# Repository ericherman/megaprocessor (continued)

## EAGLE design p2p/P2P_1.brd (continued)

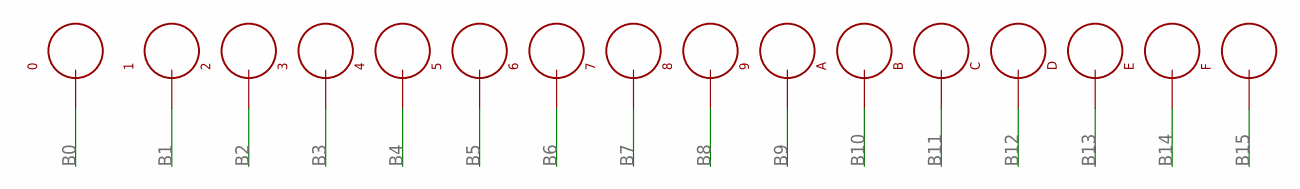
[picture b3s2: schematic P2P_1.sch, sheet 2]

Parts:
0, 1, 2, 3, 4, 5, 6, 7, 8, 9: TEST_LOOP
A: TEST_LOOP
B: TEST_LOOP
C: TEST_LOOP
D: TEST_LOOP
E: TEST_LOOP
F: TEST_LOOP

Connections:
B0: 0.P$1; also elsewhere on the board
B1: 1.P$1; also elsewhere on the board
B2: 2.P$1; also elsewhere on the board
B3: 3.P$1; also elsewhere on the board
B4: 4.P$1; also elsewhere on the board
B5: 5.P$1; also elsewhere on the board
B6: 6.P$1; also elsewhere on the board
B7: 7.P$1; also elsewhere on the board
B8: 8.P$1; also elsewhere on the board
B9: 9.P$1; also elsewhere on the board
B10: A.P$1; also elsewhere on the board
B11: B.P$1; also elsewhere on the board
B12: C.P$1; also elsewhere on the board
B13: D.P$1; also elsewhere on the board
B14: E.P$1; also elsewhere on the board
B15: F.P$1; also elsewhere on the board

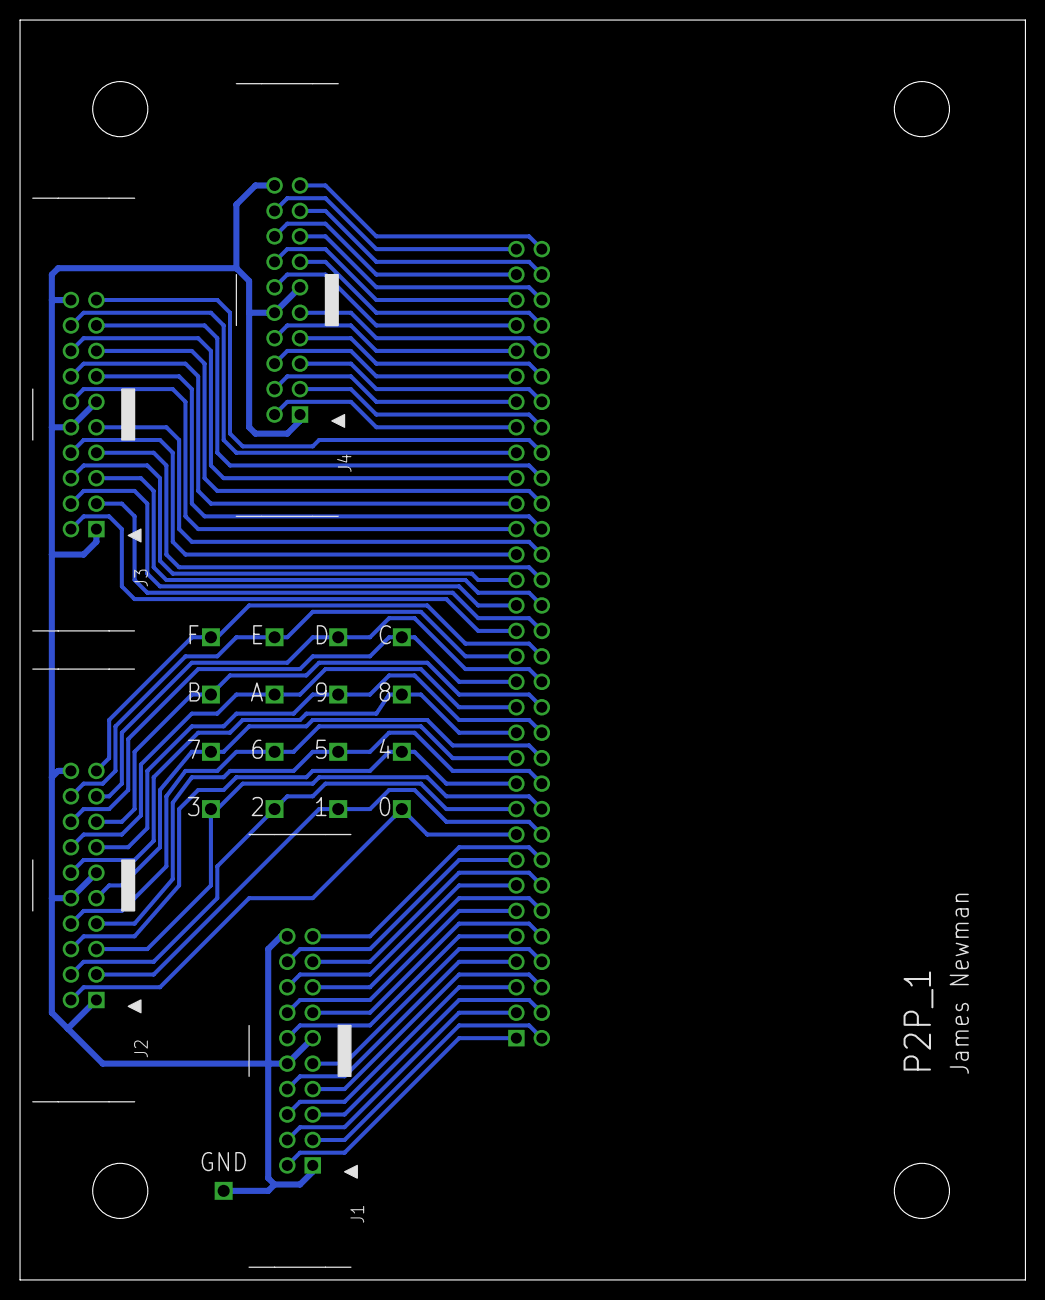
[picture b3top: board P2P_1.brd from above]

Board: 2 copper layers, 100.3 x 125.7 mm, 26 parts (1 on the bottom side), 65 nets.

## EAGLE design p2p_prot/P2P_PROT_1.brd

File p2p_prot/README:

frame to frame (protected)

Does the same as above but I added some protection circuitry for when
its used for incoming buses. I don't know if its necessary, or if I did
it correctly.

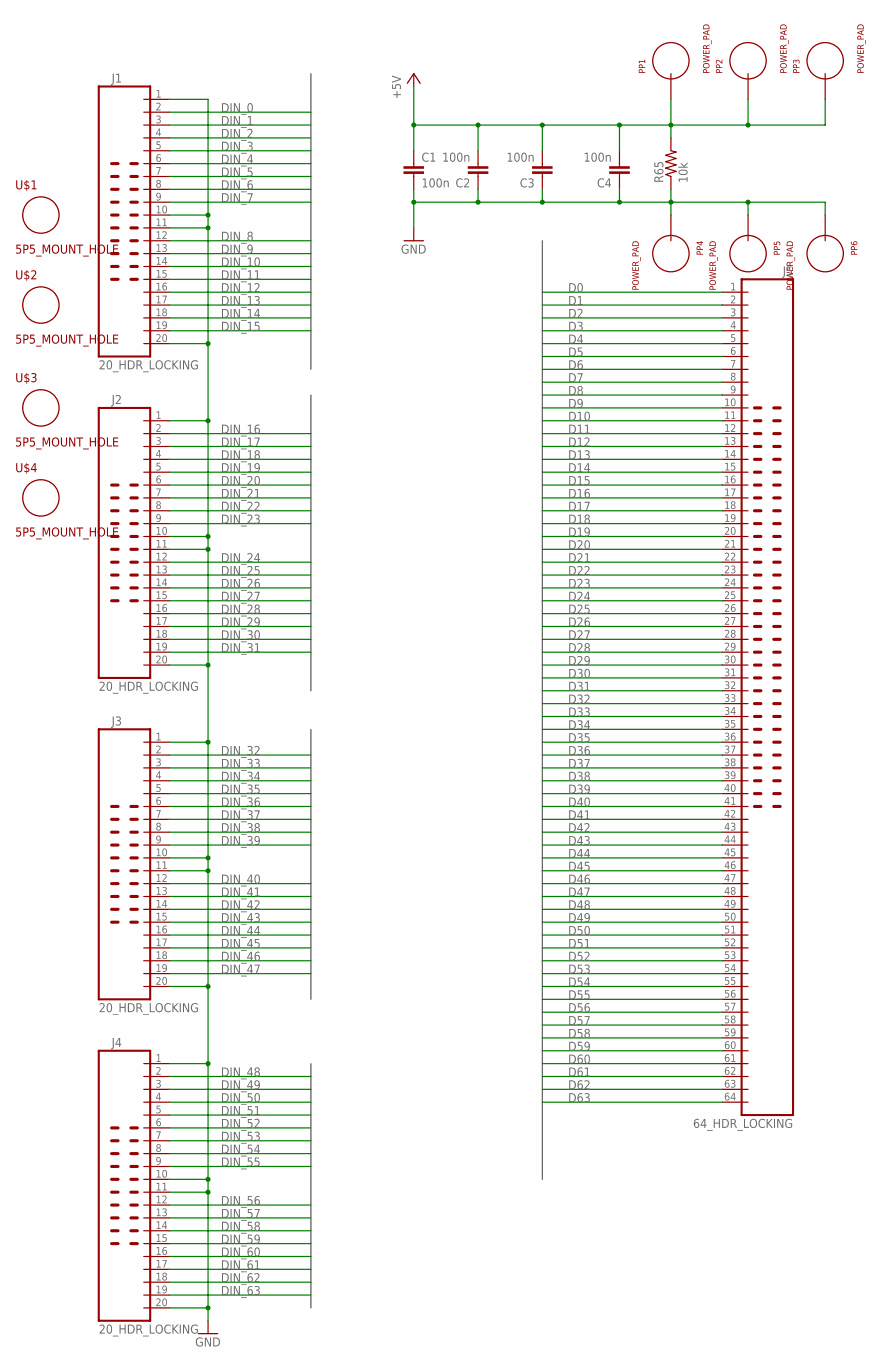
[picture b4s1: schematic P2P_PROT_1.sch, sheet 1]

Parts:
C1, C2, C3, C4: 100n; CAP_P2INCH
J1, J2, J3, J4: 20_HDR_LOCKING
J5: 64_HDR_LOCKING
PP1, PP2, PP3, PP4, PP5, PP6: POWER_PAD
R65: 10k; R_P2INCH
U$1, U$2, U$3, U$4: 5P5_MOUNT_HOLE; 5P5M_HOLE

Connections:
+5V: C1.1, C2.2, C3.2, C4.2, PP1.1, PP2.1, PP3.1, R65.2; also elsewhere on the board
D0: J5.1; also elsewhere on the board
D1: J5.2; also elsewhere on the board
D2: J5.3; also elsewhere on the board
D3: J5.4; also elsewhere on the board
D4: J5.5; also elsewhere on the board
D5: J5.6; also elsewhere on the board
D6: J5.7; also elsewhere on the board
D7: J5.8; also elsewhere on the board
D8: J5.9; also elsewhere on the board
D9: J5.10; also elsewhere on the board
D10: J5.11; also elsewhere on the board
D11: J5.12; also elsewhere on the board
D12: J5.13; also elsewhere on the board
D13: J5.14; also elsewhere on the board
D14: J5.15; also elsewhere on the board
D15: J5.16; also elsewhere on the board
D16: J5.17; also elsewhere on the board
D17: J5.18; also elsewhere on the board
D18: J5.19; also elsewhere on the board
D19: J5.20; also elsewhere on the board
D20: J5.21; also elsewhere on the board
D21: J5.22; also elsewhere on the board
D22: J5.23; also elsewhere on the board
D23: J5.24; also elsewhere on the board
D24: J5.25; also elsewhere on the board
D25: J5.26; also elsewhere on the board
D26: J5.27; also elsewhere on the board
D27: J5.28; also elsewhere on the board
D28: J5.29; also elsewhere on the board
D29: J5.30; also elsewhere on the board
D30: J5.31; also elsewhere on the board
D31: J5.32; also elsewhere on the board
D32: J5.33; also elsewhere on the board
D33: J5.34; also elsewhere on the board
D34: J5.35; also elsewhere on the board
D35: J5.36; also elsewhere on the board
D36: J5.37; also elsewhere on the board
D37: J5.38; also elsewhere on the board
D38: J5.39; also elsewhere on the board
D39: J5.40; also elsewhere on the board
D40: J5.41; also elsewhere on the board
D41: J5.42; also elsewhere on the board
D42: J5.43; also elsewhere on the board
D43: J5.44; also elsewhere on the board
D44: J5.45; also elsewhere on the board
D45: J5.46; also elsewhere on the board
D46: J5.47; also elsewhere on the board
D47: J5.48; also elsewhere on the board
D48: J5.49; also elsewhere on the board
D49: J5.50; also elsewhere on the board
D50: J5.51; also elsewhere on the board
D51: J5.52; also elsewhere on the board
D52: J5.53; also elsewhere on the board
D53: J5.54; also elsewhere on the board
D54: J5.55; also elsewhere on the board
D55: J5.56; also elsewhere on the board
D56: J5.57; also elsewhere on the board
D57: J5.58; also elsewhere on the board
D58: J5.59; also elsewhere on the board
D59: J5.60; also elsewhere on the board
D60: J5.61; also elsewhere on the board
D61: J5.62; also elsewhere on the board
D62: J5.63; also elsewhere on the board
D63: J5.64; also elsewhere on the board
DIN_0: J1.2; also elsewhere on the board
DIN_1: J1.3; also elsewhere on the board
DIN_2: J1.4; also elsewhere on the board
DIN_3: J1.5; also elsewhere on the board
DIN_4: J1.6; also elsewhere on the board
DIN_5: J1.7; also elsewhere on the board
DIN_6: J1.8; also elsewhere on the board
DIN_7: J1.9; also elsewhere on the board
DIN_8: J1.12; also elsewhere on the board
DIN_9: J1.13; also elsewhere on the board
DIN_10: J1.14; also elsewhere on the board
DIN_11: J1.15; also elsewhere on the board
DIN_12: J1.16; also elsewhere on the board
DIN_13: J1.17; also elsewhere on the board
DIN_14: J1.18; also elsewhere on the board
DIN_15: J1.19; also elsewhere on the board
DIN_16: J2.2; also elsewhere on the board
DIN_17: J2.3; also elsewhere on the board
DIN_18: J2.4; also elsewhere on the board
DIN_19: J2.5; also elsewhere on the board
DIN_20: J2.6; also elsewhere on the board
DIN_21: J2.7; also elsewhere on the board
DIN_22: J2.8; also elsewhere on the board
DIN_23: J2.9; also elsewhere on the board
DIN_24: J2.12; also elsewhere on the board
DIN_25: J2.13; also elsewhere on the board
DIN_26: J2.14; also elsewhere on the board
DIN_27: J2.15; also elsewhere on the board
DIN_28: J2.16; also elsewhere on the board
DIN_29: J2.17; also elsewhere on the board
DIN_30: J2.18; also elsewhere on the board
DIN_31: J2.19; also elsewhere on the board
DIN_32: J3.2; also elsewhere on the board
DIN_33: J3.3; also elsewhere on the board
DIN_34: J3.4; also elsewhere on the board
DIN_35: J3.5; also elsewhere on the board
DIN_36: J3.6; also elsewhere on the board
DIN_37: J3.7; also elsewhere on the board
DIN_38: J3.8; also elsewhere on the board
DIN_39: J3.9; also elsewhere on the board
DIN_40: J3.12; also elsewhere on the board
DIN_41: J3.13; also elsewhere on the board
DIN_42: J3.14; also elsewhere on the board
DIN_43: J3.15; also elsewhere on the board
DIN_44: J3.16; also elsewhere on the board
DIN_45: J3.17; also elsewhere on the board
DIN_46: J3.18; also elsewhere on the board
DIN_47: J3.19; also elsewhere on the board
DIN_48: J4.2; also elsewhere on the board
DIN_49: J4.3; also elsewhere on the board
DIN_50: J4.4; also elsewhere on the board
DIN_51: J4.5; also elsewhere on the board
DIN_52: J4.6; also elsewhere on the board
DIN_53: J4.7; also elsewhere on the board
DIN_54: J4.8; also elsewhere on the board
DIN_55: J4.9; also elsewhere on the board
DIN_56: J4.12; also elsewhere on the board
DIN_57: J4.13; also elsewhere on the board
DIN_58: J4.14; also elsewhere on the board
DIN_59: J4.15; also elsewhere on the board
DIN_60: J4.16; also elsewhere on the board
DIN_61: J4.17; also elsewhere on the board
DIN_62: J4.18; also elsewhere on the board
DIN_63: J4.19; also elsewhere on the board
GND: C1.2, C2.1, C3.1, C4.1, J1.1, J1.10, J1.11, J1.20, J2.1, J2.10, J2.11, J2.20, J3.1, J3.10, J3.11, J3.20, J4.1, J4.10, J4.11, J4.20, PP4.1, PP5.1, PP6.1, R65.1; also elsewhere on the board

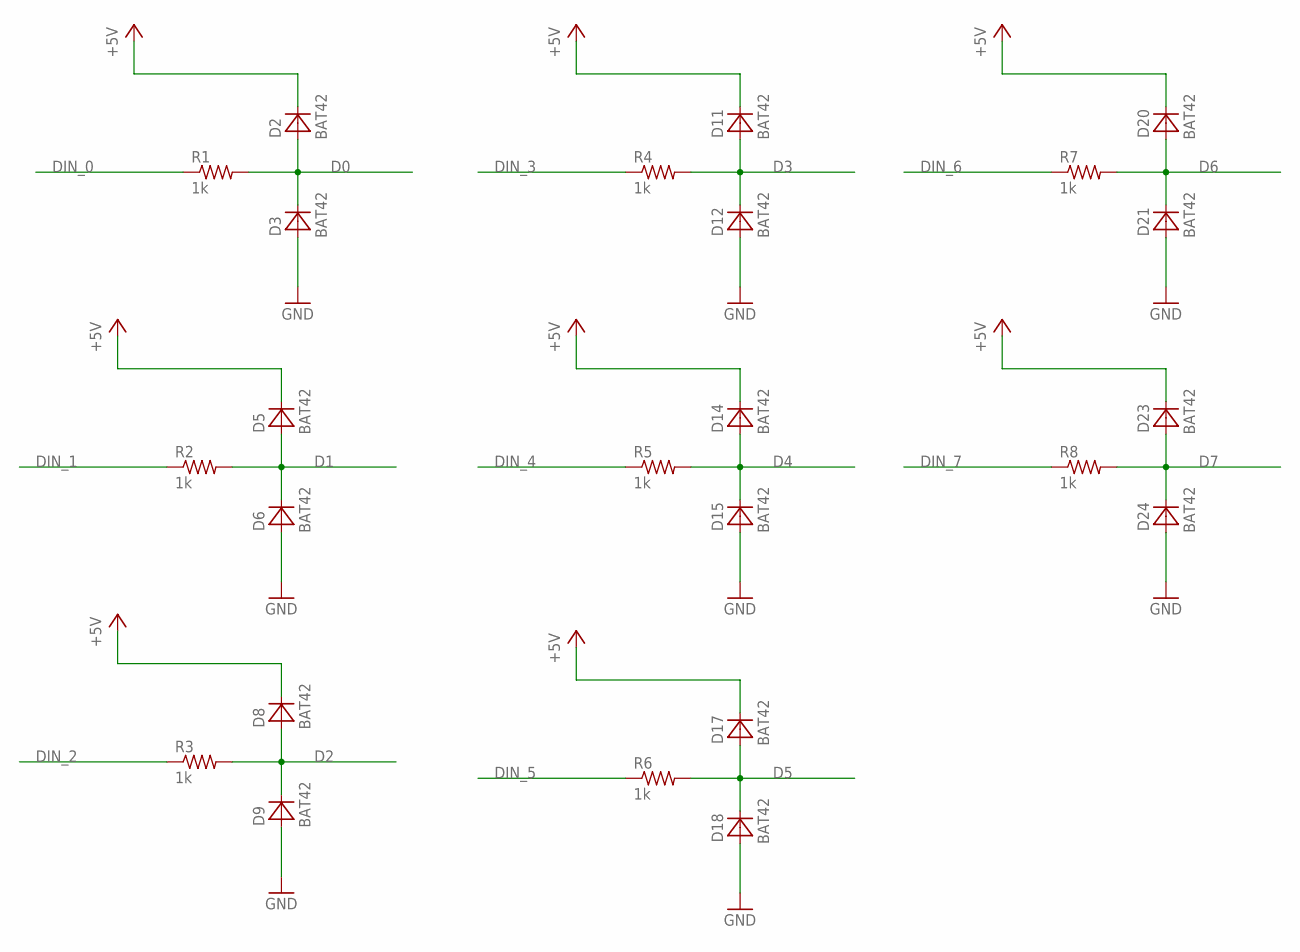
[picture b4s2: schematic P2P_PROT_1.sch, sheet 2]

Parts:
D2, D3, D5, D6, D8, D9, D11, D12, D14, D15, D17, D18, D20, D21, D23, D24: BAT42; DO34-5
R1, R2, R3, R4, R5, R6, R7, R8: 1k; R_P2INCH

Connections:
+5V: D2.C, D5.C, D8.C, D11.C, D14.C, D17.C, D20.C, D23.C; also elsewhere on the board
D0: D2.A, D3.C, R1.2; also elsewhere on the board
D1: D5.A, D6.C, R2.2; also elsewhere on the board
D2: D8.A, D9.C, R3.2; also elsewhere on the board
D3: D11.A, D12.C, R4.2; also elsewhere on the board
D4: D14.A, D15.C, R5.2; also elsewhere on the board
D5: D17.A, D18.C, R6.2; also elsewhere on the board
D6: D20.A, D21.C, R7.2; also elsewhere on the board
D7: D23.A, D24.C, R8.2; also elsewhere on the board
DIN_0: R1.1; also elsewhere on the board
DIN_1: R2.1; also elsewhere on the board
DIN_2: R3.1; also elsewhere on the board
DIN_3: R4.1; also elsewhere on the board
DIN_4: R5.1; also elsewhere on the board
DIN_5: R6.1; also elsewhere on the board
DIN_6: R7.1; also elsewhere on the board
DIN_7: R8.1; also elsewhere on the board
GND: D3.A, D6.A, D9.A, D12.A, D15.A, D18.A, D21.A, D24.A; also elsewhere on the board

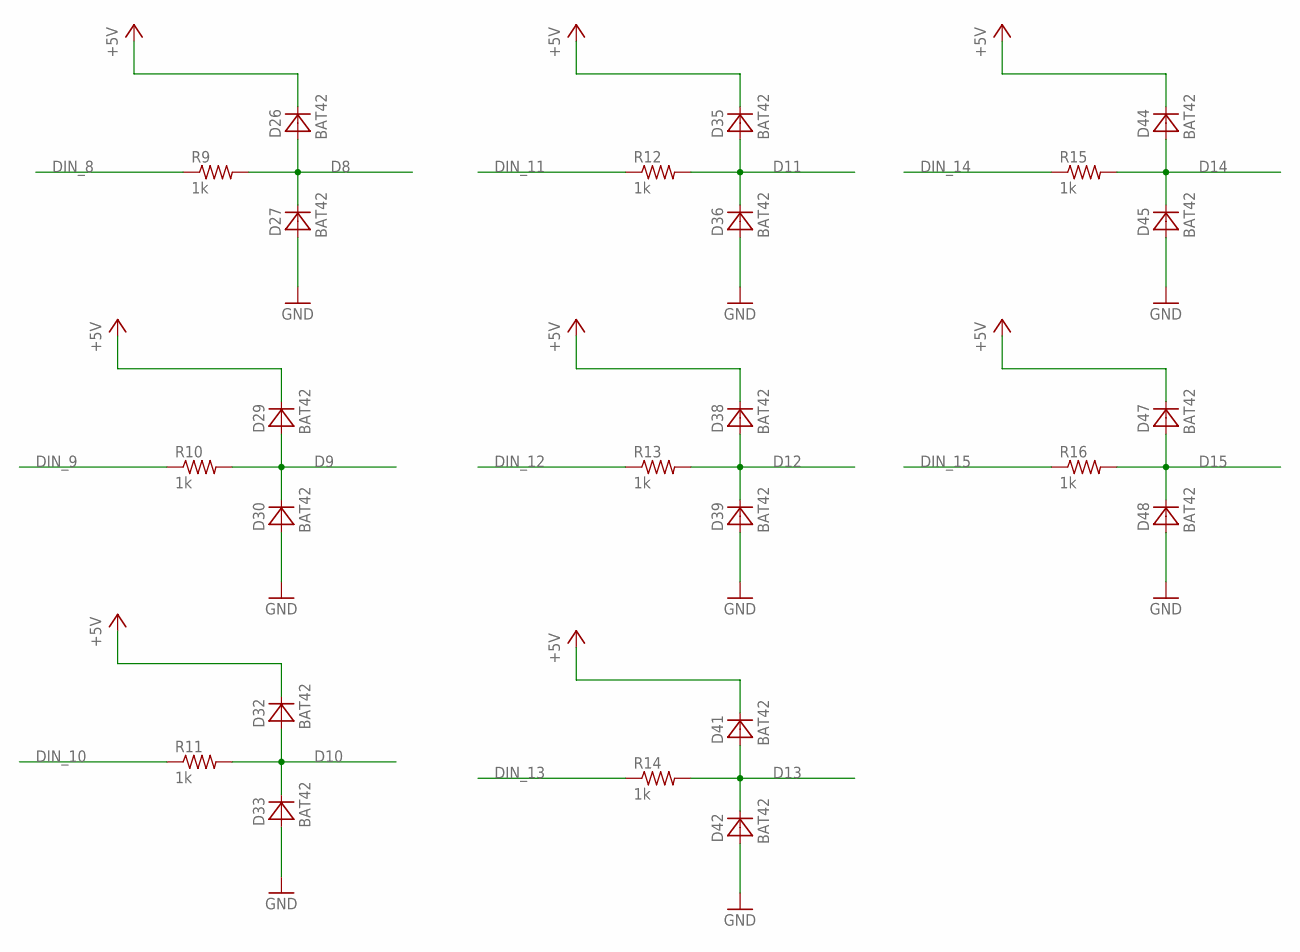
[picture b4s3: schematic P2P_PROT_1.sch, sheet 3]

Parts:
D26, D27, D29, D30, D32, D33, D35, D36, D38, D39, D41, D42, D44, D45, D47, D48: BAT42; DO34-5
R9, R10, R11, R12, R13, R14, R15, R16: 1k; R_P2INCH

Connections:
+5V: D26.C, D29.C, D32.C, D35.C, D38.C, D41.C, D44.C, D47.C; also elsewhere on the board
D8: D26.A, D27.C, R9.2; also elsewhere on the board
D9: D29.A, D30.C, R10.2; also elsewhere on the board
D10: D32.A, D33.C, R11.2; also elsewhere on the board
D11: D35.A, D36.C, R12.2; also elsewhere on the board
D12: D38.A, D39.C, R13.2; also elsewhere on the board
D13: D41.A, D42.C, R14.2; also elsewhere on the board
D14: D44.A, D45.C, R15.2; also elsewhere on the board
D15: D47.A, D48.C, R16.2; also elsewhere on the board
DIN_8: R9.1; also elsewhere on the board
DIN_9: R10.1; also elsewhere on the board
DIN_10: R11.1; also elsewhere on the board
DIN_11: R12.1; also elsewhere on the board
DIN_12: R13.1; also elsewhere on the board
DIN_13: R14.1; also elsewhere on the board
DIN_14: R15.1; also elsewhere on the board
DIN_15: R16.1; also elsewhere on the board
GND: D27.A, D30.A, D33.A, D36.A, D39.A, D42.A, D45.A, D48.A; also elsewhere on the board

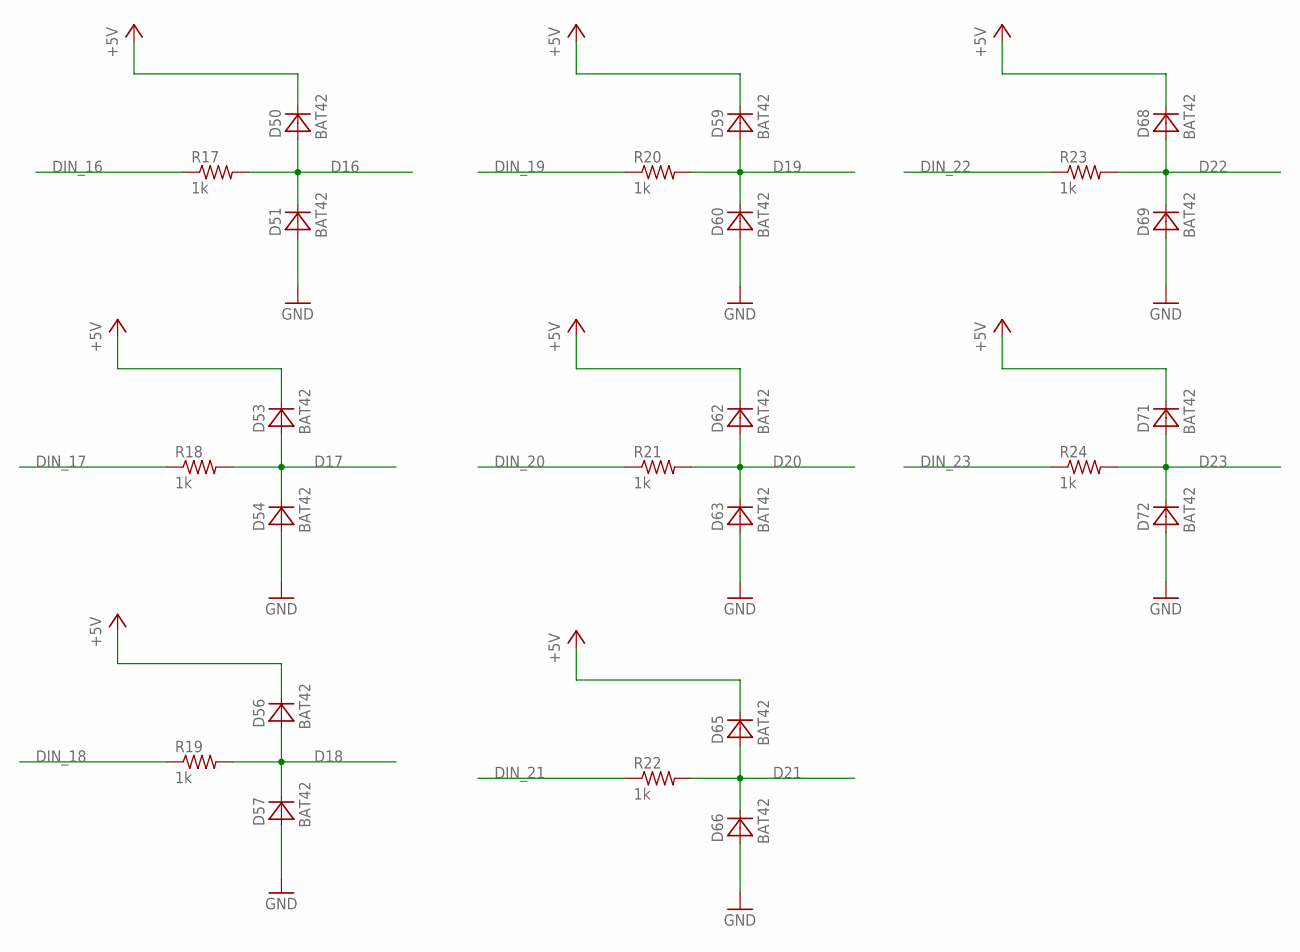
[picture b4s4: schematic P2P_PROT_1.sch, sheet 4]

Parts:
D50, D51, D53, D54, D56, D57, D59, D60, D62, D63, D65, D66, D68, D69, D71, D72: BAT42; DO34-5
R17, R18, R19, R20, R21, R22, R23, R24: 1k; R_P2INCH

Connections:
+5V: D50.C, D53.C, D56.C, D59.C, D62.C, D65.C, D68.C, D71.C; also elsewhere on the board
D16: D50.A, D51.C, R17.2; also elsewhere on the board
D17: D53.A, D54.C, R18.2; also elsewhere on the board
D18: D56.A, D57.C, R19.2; also elsewhere on the board
D19: D59.A, D60.C, R20.2; also elsewhere on the board
D20: D62.A, D63.C, R21.2; also elsewhere on the board
D21: D65.A, D66.C, R22.2; also elsewhere on the board
D22: D68.A, D69.C, R23.2; also elsewhere on the board
D23: D71.A, D72.C, R24.2; also elsewhere on the board
DIN_16: R17.1; also elsewhere on the board
DIN_17: R18.1; also elsewhere on the board
DIN_18: R19.1; also elsewhere on the board
DIN_19: R20.1; also elsewhere on the board
DIN_20: R21.1; also elsewhere on the board
DIN_21: R22.1; also elsewhere on the board
DIN_22: R23.1; also elsewhere on the board
DIN_23: R24.1; also elsewhere on the board
GND: D51.A, D54.A, D57.A, D60.A, D63.A, D66.A, D69.A, D72.A; also elsewhere on the board

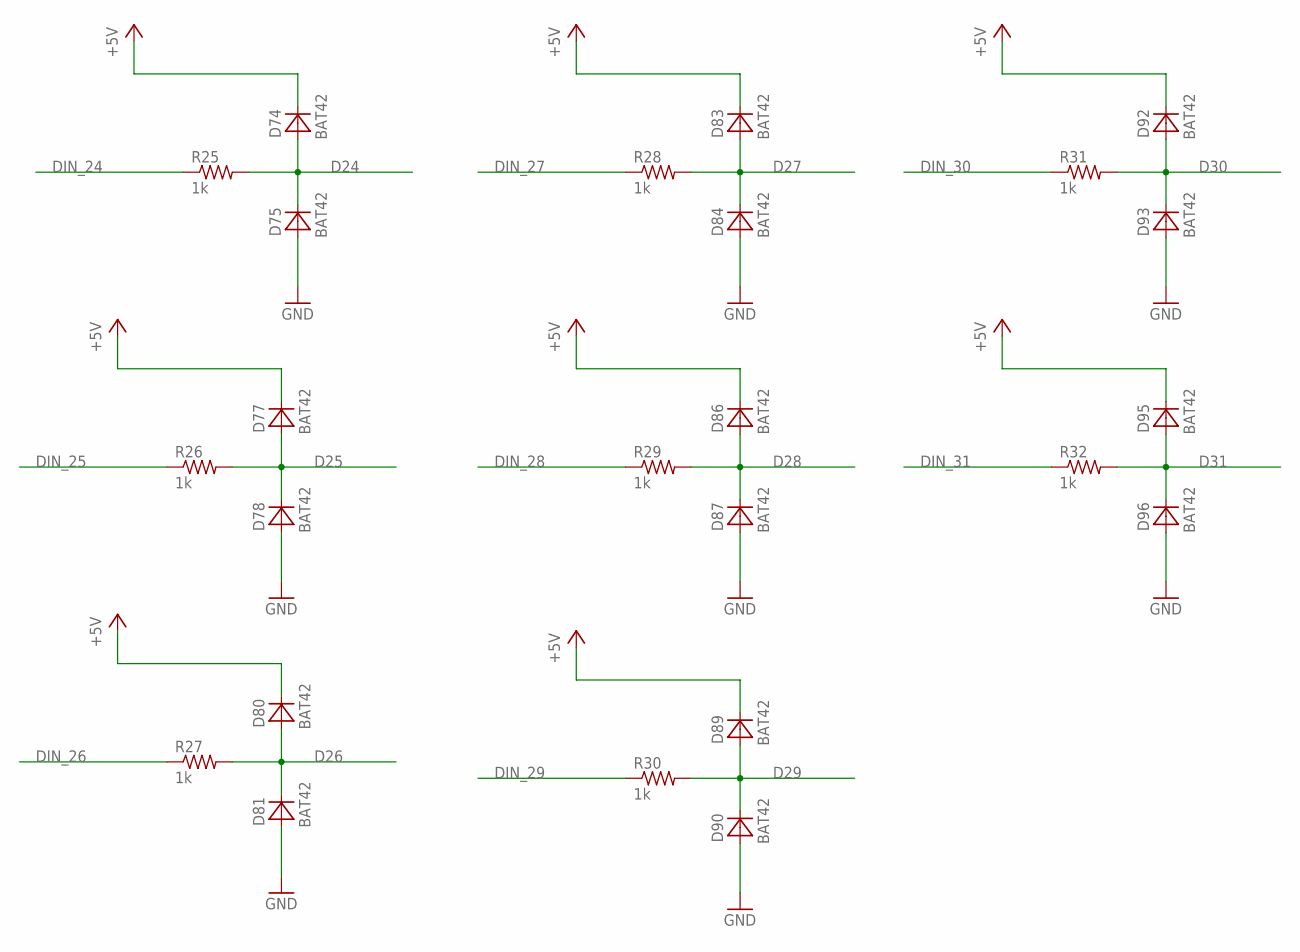
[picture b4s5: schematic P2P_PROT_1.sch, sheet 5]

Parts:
D74, D75, D77, D78, D80, D81, D83, D84, D86, D87, D89, D90, D92, D93, D95, D96: BAT42; DO34-5
R25, R26, R27, R28, R29, R30, R31, R32: 1k; R_P2INCH

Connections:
+5V: D74.C, D77.C, D80.C, D83.C, D86.C, D89.C, D92.C, D95.C; also elsewhere on the board
D24: D74.A, D75.C, R25.2; also elsewhere on the board
D25: D77.A, D78.C, R26.2; also elsewhere on the board
D26: D80.A, D81.C, R27.2; also elsewhere on the board
D27: D83.A, D84.C, R28.2; also elsewhere on the board
D28: D86.A, D87.C, R29.2; also elsewhere on the board
D29: D89.A, D90.C, R30.2; also elsewhere on the board
D30: D92.A, D93.C, R31.2; also elsewhere on the board
D31: D95.A, D96.C, R32.2; also elsewhere on the board
DIN_24: R25.1; also elsewhere on the board
DIN_25: R26.1; also elsewhere on the board
DIN_26: R27.1; also elsewhere on the board
DIN_27: R28.1; also elsewhere on the board
DIN_28: R29.1; also elsewhere on the board
DIN_29: R30.1; also elsewhere on the board
DIN_30: R31.1; also elsewhere on the board
DIN_31: R32.1; also elsewhere on the board
GND: D75.A, D78.A, D81.A, D84.A, D87.A, D90.A, D93.A, D96.A; also elsewhere on the board

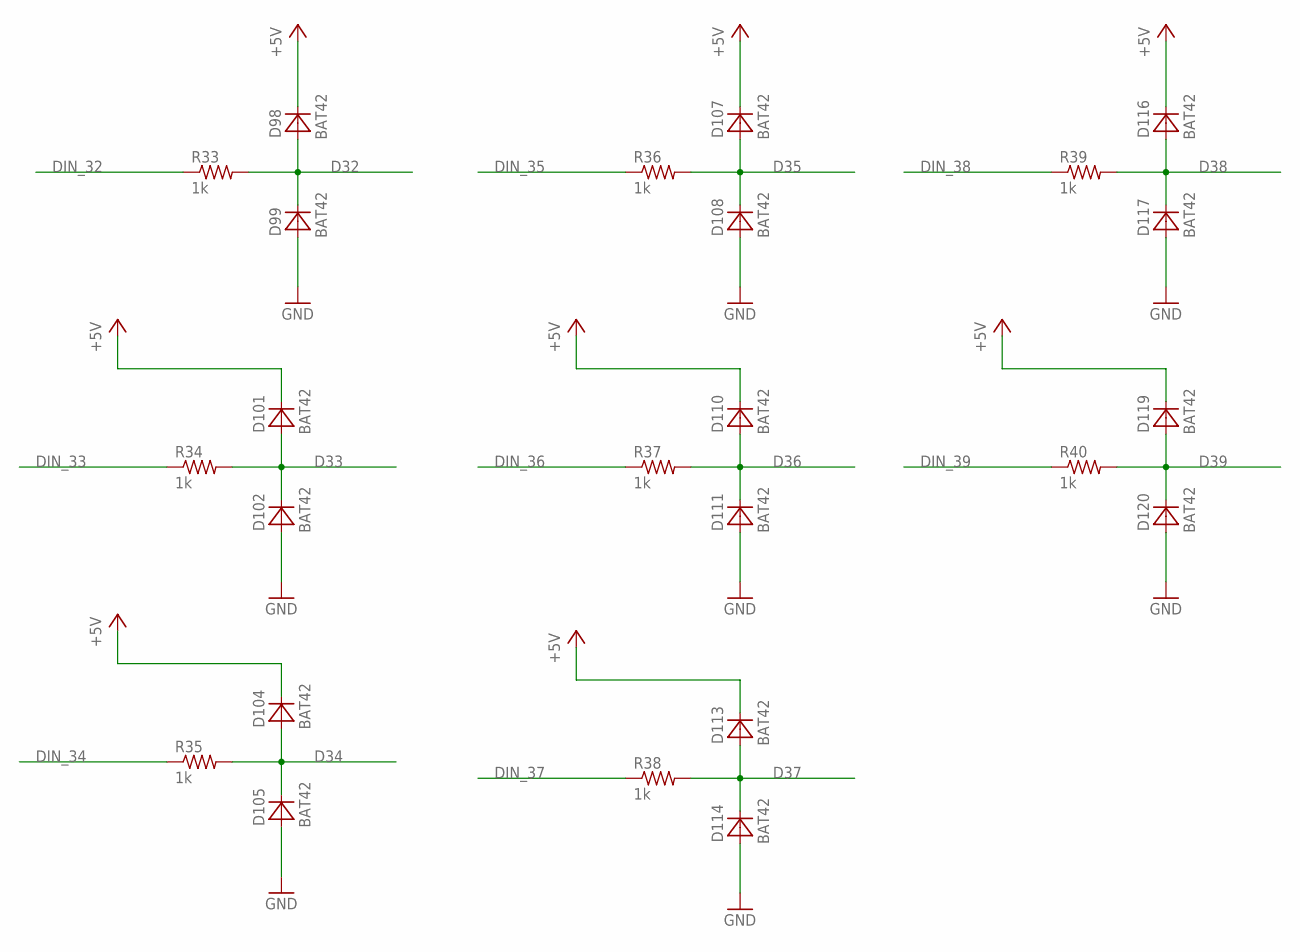
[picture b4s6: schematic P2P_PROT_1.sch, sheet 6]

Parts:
D98, D99, D101, D102, D104, D105, D107, D108, D110, D111, D113, D114, D116, D117, D119, D120: BAT42; DO34-5
R33, R34, R35, R36, R37, R38, R39, R40: 1k; R_P2INCH

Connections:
+5V: D98.C, D101.C, D104.C, D107.C, D110.C, D113.C, D116.C, D119.C; also elsewhere on the board
D32: D98.A, D99.C, R33.2; also elsewhere on the board
D33: D101.A, D102.C, R34.2; also elsewhere on the board
D34: D104.A, D105.C, R35.2; also elsewhere on the board
D35: D107.A, D108.C, R36.2; also elsewhere on the board
D36: D110.A, D111.C, R37.2; also elsewhere on the board
D37: D113.A, D114.C, R38.2; also elsewhere on the board
D38: D116.A, D117.C, R39.2; also elsewhere on the board
D39: D119.A, D120.C, R40.2; also elsewhere on the board
DIN_32: R33.1; also elsewhere on the board
DIN_33: R34.1; also elsewhere on the board
DIN_34: R35.1; also elsewhere on the board
DIN_35: R36.1; also elsewhere on the board
DIN_36: R37.1; also elsewhere on the board
DIN_37: R38.1; also elsewhere on the board
DIN_38: R39.1; also elsewhere on the board
DIN_39: R40.1; also elsewhere on the board
GND: D99.A, D102.A, D105.A, D108.A, D111.A, D114.A, D117.A, D120.A; also elsewhere on the board

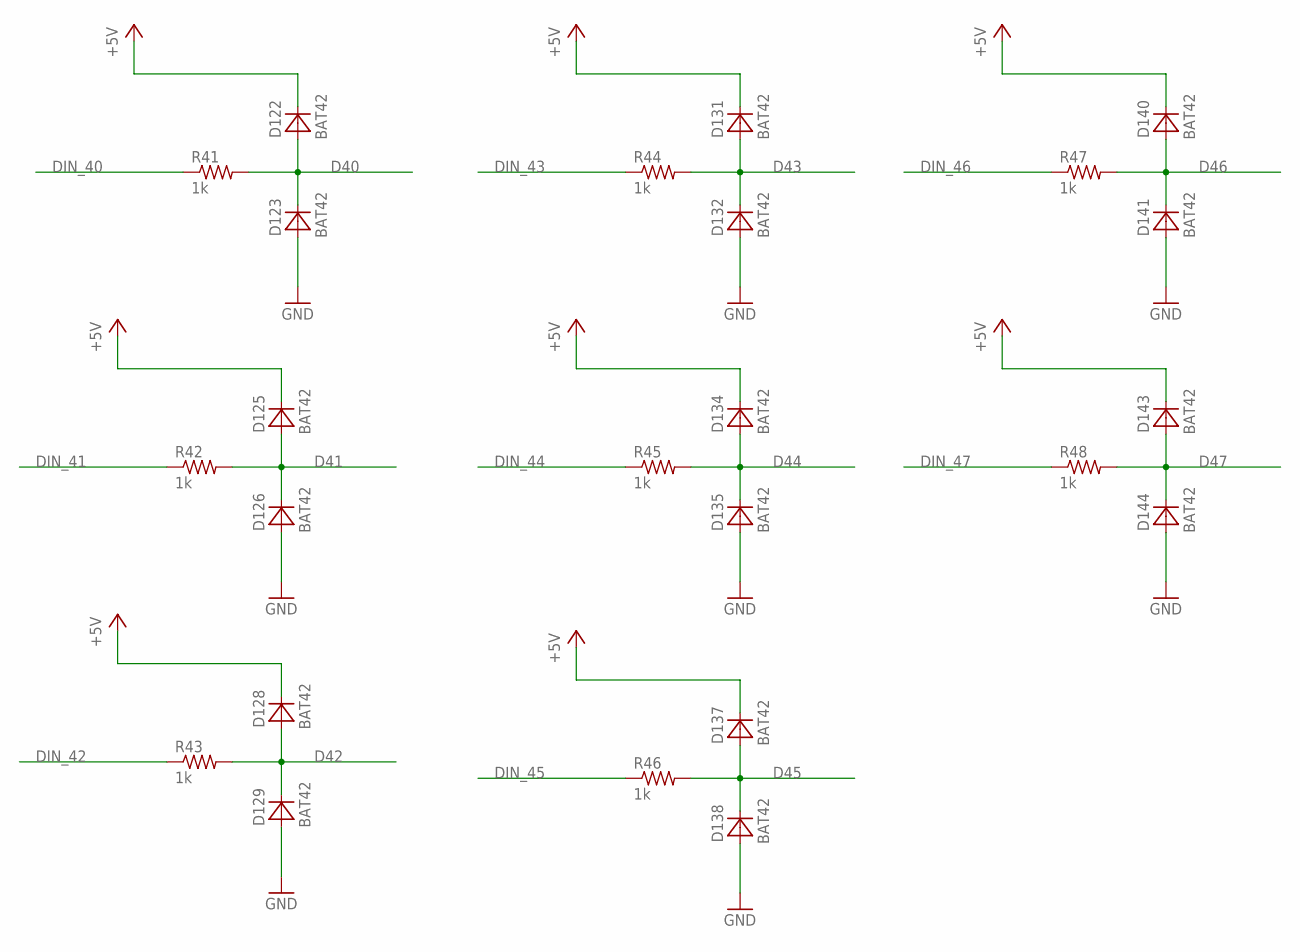
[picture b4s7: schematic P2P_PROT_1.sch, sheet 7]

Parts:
D122, D123, D125, D126, D128, D129, D131, D132, D134, D135, D137, D138, D140, D141, D143, D144: BAT42; DO34-5
R41, R42, R43, R44, R45, R46, R47, R48: 1k; R_P2INCH

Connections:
+5V: D122.C, D125.C, D128.C, D131.C, D134.C, D137.C, D140.C, D143.C; also elsewhere on the board
D40: D122.A, D123.C, R41.2; also elsewhere on the board
D41: D125.A, D126.C, R42.2; also elsewhere on the board
D42: D128.A, D129.C, R43.2; also elsewhere on the board
D43: D131.A, D132.C, R44.2; also elsewhere on the board
D44: D134.A, D135.C, R45.2; also elsewhere on the board
D45: D137.A, D138.C, R46.2; also elsewhere on the board
D46: D140.A, D141.C, R47.2; also elsewhere on the board
D47: D143.A, D144.C, R48.2; also elsewhere on the board
DIN_40: R41.1; also elsewhere on the board
DIN_41: R42.1; also elsewhere on the board
DIN_42: R43.1; also elsewhere on the board
DIN_43: R44.1; also elsewhere on the board
DIN_44: R45.1; also elsewhere on the board
DIN_45: R46.1; also elsewhere on the board
DIN_46: R47.1; also elsewhere on the board
DIN_47: R48.1; also elsewhere on the board
GND: D123.A, D126.A, D129.A, D132.A, D135.A, D138.A, D141.A, D144.A; also elsewhere on the board

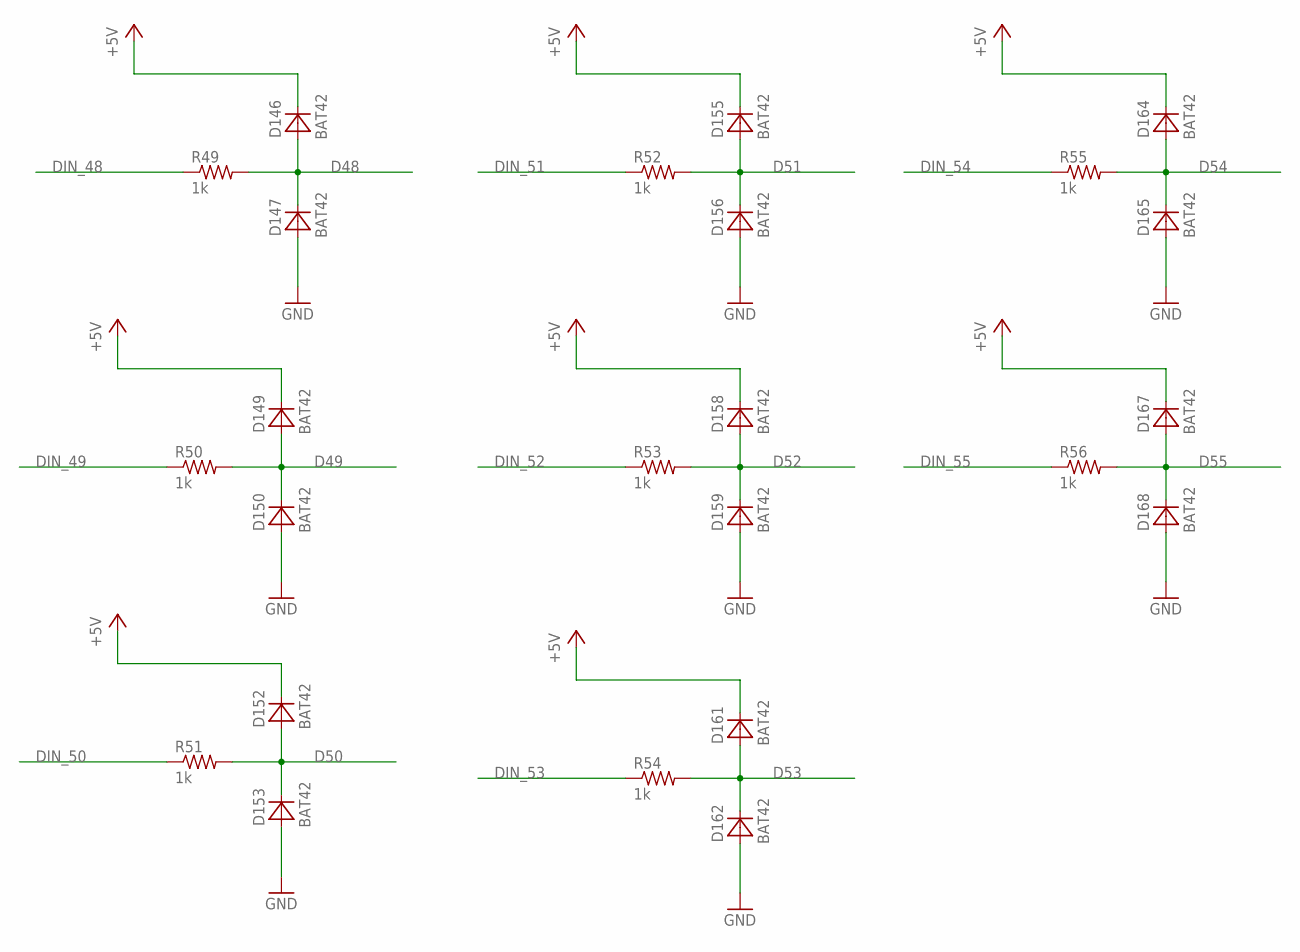
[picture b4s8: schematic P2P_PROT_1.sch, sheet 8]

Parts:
D146, D147, D149, D150, D152, D153, D155, D156, D158, D159, D161, D162, D164, D165, D167, D168: BAT42; DO34-5
R49, R50, R51, R52, R53, R54, R55, R56: 1k; R_P2INCH

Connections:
+5V: D146.C, D149.C, D152.C, D155.C, D158.C, D161.C, D164.C, D167.C; also elsewhere on the board
D48: D146.A, D147.C, R49.2; also elsewhere on the board
D49: D149.A, D150.C, R50.2; also elsewhere on the board
D50: D152.A, D153.C, R51.2; also elsewhere on the board
D51: D155.A, D156.C, R52.2; also elsewhere on the board
D52: D158.A, D159.C, R53.2; also elsewhere on the board
D53: D161.A, D162.C, R54.2; also elsewhere on the board
D54: D164.A, D165.C, R55.2; also elsewhere on the board
D55: D167.A, D168.C, R56.2; also elsewhere on the board
DIN_48: R49.1; also elsewhere on the board
DIN_49: R50.1; also elsewhere on the board
DIN_50: R51.1; also elsewhere on the board
DIN_51: R52.1; also elsewhere on the board
DIN_52: R53.1; also elsewhere on the board
DIN_53: R54.1; also elsewhere on the board
DIN_54: R55.1; also elsewhere on the board
DIN_55: R56.1; also elsewhere on the board
GND: D147.A, D150.A, D153.A, D156.A, D159.A, D162.A, D165.A, D168.A; also elsewhere on the board

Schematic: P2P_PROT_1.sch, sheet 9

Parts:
D170, D171, D173, D174, D176, D177, D179, D180, D182, D183, D185, D186, D188, D189, D191, D192: BAT42; DO34-5
R57, R58, R59, R60, R61, R62, R63, R64: 1k; R_P2INCH

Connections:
+5V: D170.C, D173.C, D176.C, D179.C, D182.C, D185.C, D188.C, D191.C; also elsewhere on the board
D56: D170.A, D171.C, R57.2; also elsewhere on the board
D57: D173.A, D174.C, R58.2; also elsewhere on the board
D58: D176.A, D177.C, R59.2; also elsewhere on the board
D59: D179.A, D180.C, R60.2; also elsewhere on the board
D60: D182.A, D183.C, R61.2; also elsewhere on the board
D61: D185.A, D186.C, R62.2; also elsewhere on the board
D62: D188.A, D189.C, R63.2; also elsewhere on the board
D63: D191.A, D192.C, R64.2; also elsewhere on the board
DIN_56: R57.1; also elsewhere on the board
DIN_57: R58.1; also elsewhere on the board
DIN_58: R59.1; also elsewhere on the board
DIN_59: R60.1; also elsewhere on the board
DIN_60: R61.1; also elsewhere on the board
DIN_61: R62.1; also elsewhere on the board
DIN_62: R63.1; also elsewhere on the board
DIN_63: R64.1; also elsewhere on the board
GND: D171.A, D174.A, D177.A, D180.A, D183.A, D186.A, D189.A, D192.A; also elsewhere on the board

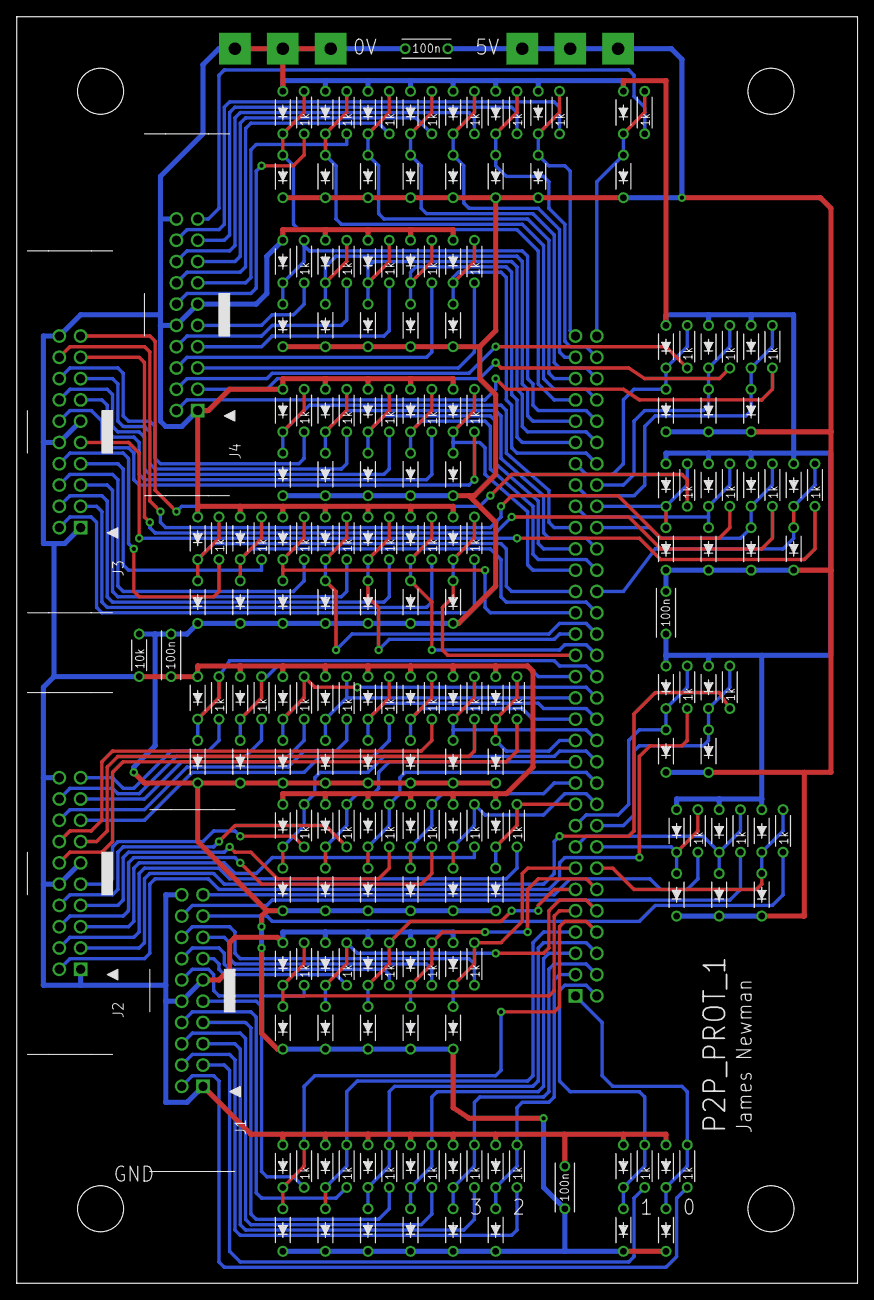
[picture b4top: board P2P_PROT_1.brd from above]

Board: 2 copper layers, 100.3 x 151.1 mm, 212 parts (1 on the bottom side), 130 nets.
